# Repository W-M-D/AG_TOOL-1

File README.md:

# AG_TOOL-1

One of my first from scratch electronic projects was a electrical ac heater with a thermocouple based control system. After needing some for work I decided to see if I could find a premade solution. I was very disappointed with my search. They all cost thousands of dollars and lacked raspberry pis. Since then I have set out to create an open source all-in-one heating system with logging and automatic control ( timing controlled runs auto shutoff etc). This is what I have come up with so far.

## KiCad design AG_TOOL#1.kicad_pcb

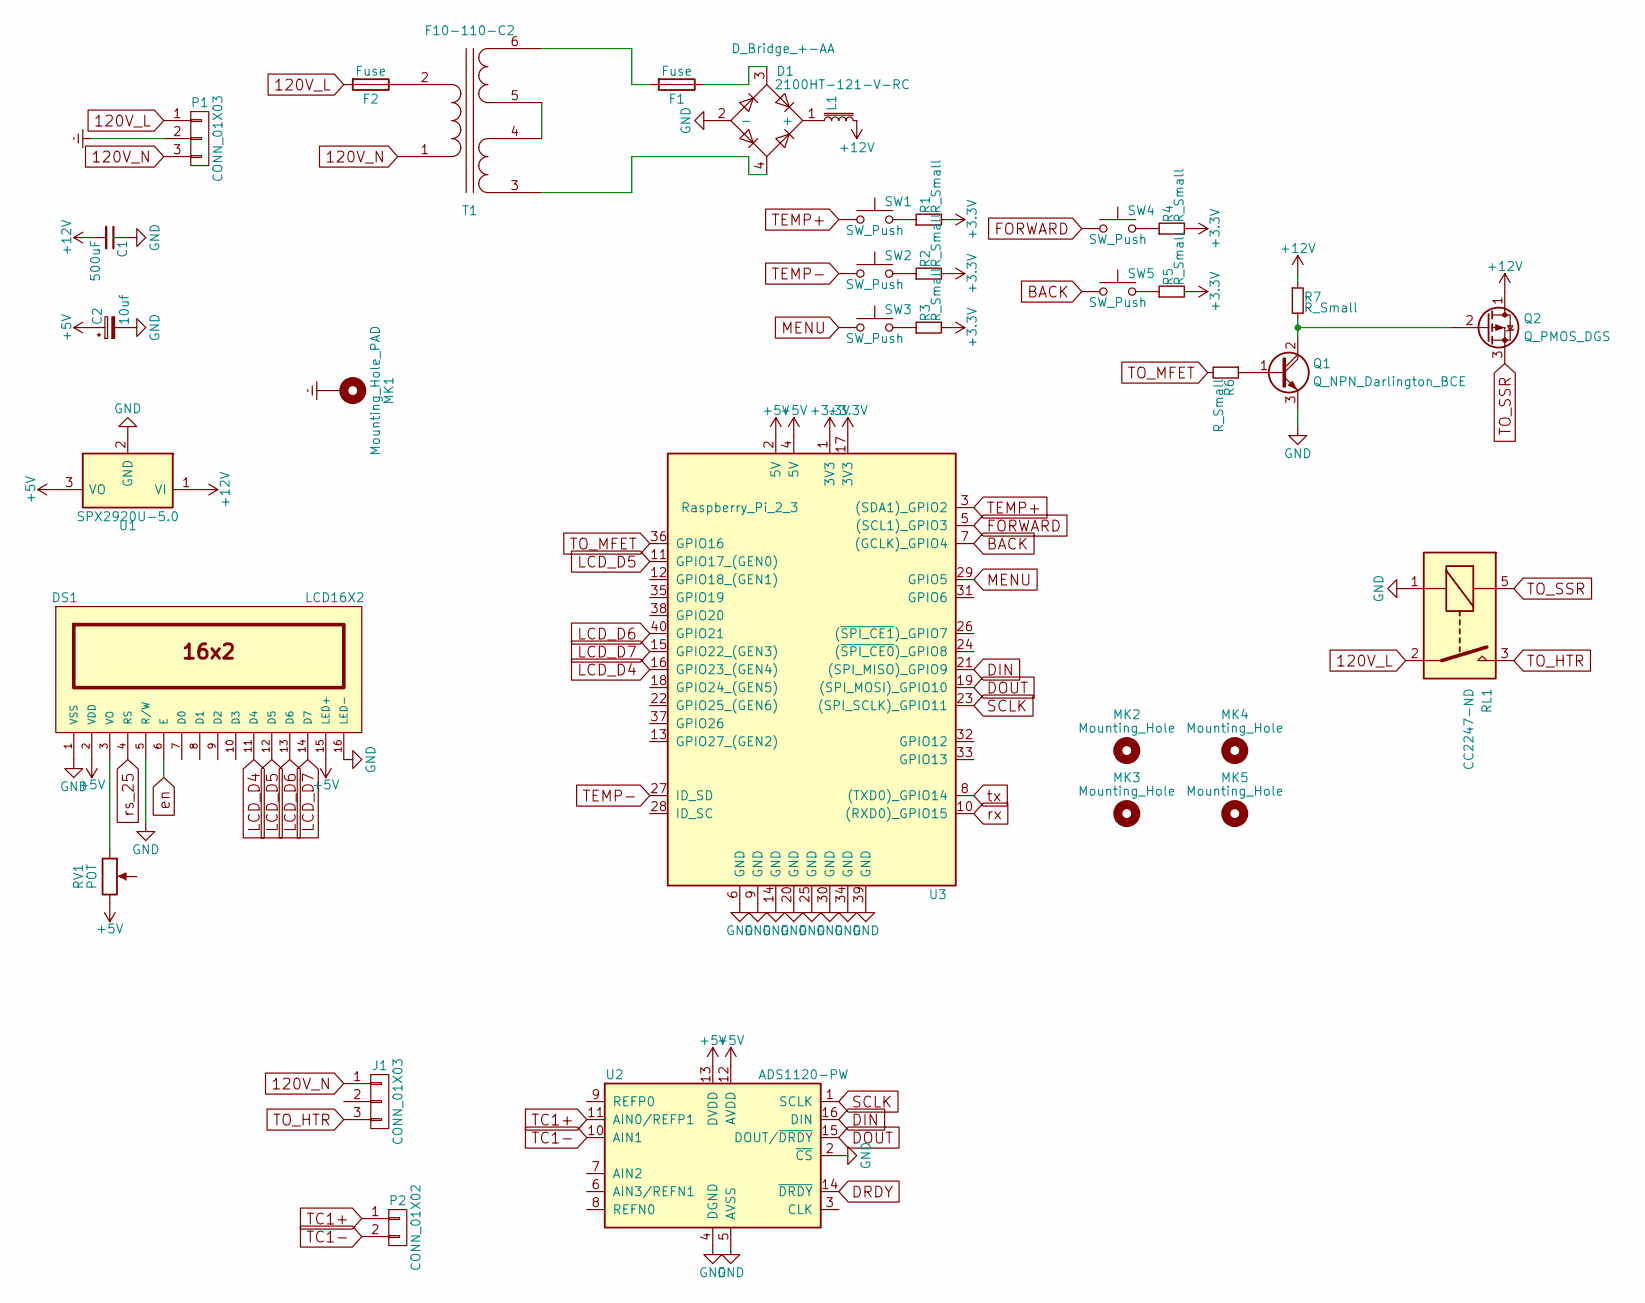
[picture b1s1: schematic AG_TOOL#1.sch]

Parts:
C1: 500uF; CP_Radial_D10.0mm_P3.50mm
C2: 10uf; C_1206
D1: D_Bridge_+-AA; Diode_Bridge_15.7x15.7
DS1: LCD16X2; Pin_Header_Straight_2x08_Pitch2.00mm
F1: Fuse; Fuse_0679H
F2: Fuse; Fuseholder_ATO_Blade_littlefuse_Pudenz_2_Pin
J1: CONN_01X03; SDF-30J
L1: 2100HT-121-V-RC; Choke_Toroid_horizontal_Diameter3-5mm_Amidon-T12
MK1: Mounting_Hole_PAD; MountingHole_4mm
MK2, MK3, MK4, MK5: Mounting_Hole; MountingHole_4mm
P1: CONN_01X03; 703W-0053
P2: CONN_01X02; K_ANSI_THERMOCOUPLE_SOCKET_PCB
Q1: Q_NPN_Darlington_BCE; SOT-23
Q2: Q_PMOS_DGS; SOT-23
R1, R2, R3, R4, R5, R6, R7: R_Small; R_0402
RL1: CC2247-ND; MCX240A5R
RV1: POT; Potentiometer_Bourns_3005_Angular_ScrewFront
SW1, SW2, SW3, SW4, SW5: SW_Push; SW_SPST_B3S-1000
T1: F10-110-C2
U1: SPX2920U-5.0; SOT-223-3Lead_TabPin2
U2: ADS1120-PW; TSSOP-16_4.4x5mm_Pitch0.65mm
U3: Raspberry_Pi_2_3; Pin_Header_Angled_2x20_Pitch2.00mm

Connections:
120V_L: F2.2, P1.1, RL1.2
120V_N: J1.1, P1.3, T1.1 (AA)
+3V3: R1.2, R2.2, R3.2, R4.2, R5.2, U3.1 (3V3), U3.17 (3V3)
+5V: C2.1, DS1.2 (VDD), DS1.15 (LED+), RV1.3, U1.3 (VO), U2.12 (AVDD), U2.13 (DVDD), U3.2 (5V), U3.4 (5V)
+12V: C1.2, L1.2, Q2.1 (D), R7.1, U1.1 (VI)
BACK: SW5.1, U3.7 ((GCLK)_GPIO4)
DIN: U2.16 (DIN), U3.21 ((SPI_MISO)_GPIO9)
DOUT: U2.15 (DOUT/~DRDY), U3.19 ((SPI_MOSI)_GPIO10)
DRDY: U2.14 (~DRDY)
Earth: MK1.1, P1.2
FORWARD: SW4.1, U3.5 ((SCL1)_GPIO3)
GND: C1.1, C2.2, D1.2 (-), DS1.1 (VSS), DS1.5 (R/W), DS1.16 (LED-), Q1.3 (E), RL1.1, U1.2 (GND), U2.2 (~CS), U2.4 (DGND), U2.5 (AVSS), U3.6 (GND), U3.9 (GND), U3.14 (GND), U3.20 (GND), U3.25 (GND), U3.30 (GND), U3.34 (GND), U3.39 (GND)
LCD_D4: DS1.11 (D4), U3.16 (GPIO23_(GEN4))
LCD_D5: DS1.12 (D5), U3.11 (GPIO17_(GEN0))
LCD_D6: DS1.13 (D6), U3.40 (GPIO21)
LCD_D7: DS1.14 (D7), U3.15 (GPIO22_(GEN3))
MENU: SW3.1, U3.29 (GPIO5)
unnamed: D1.1 (+), L1.1
unnamed: D1.3, F1.1
unnamed: D1.4, T1.3 (SA)
unnamed: DS1.3 (VO), RV1.1
unnamed: F1.2, T1.6 (SD)
unnamed: F2.1, T1.2 (AB)
unnamed: Q1.1 (B), R6.1
unnamed: Q1.2 (C), Q2.2 (G), R7.2
unnamed: R1.1, SW1.2
unnamed: R2.1, SW2.2
unnamed: R3.1, SW3.2
unnamed: R4.1, SW4.2
unnamed: R5.1, SW5.2
unnamed: T1.4 (SB), T1.5 (SC)
SCLK: U2.1 (SCLK), U3.23 ((SPI_SCLK)_GPIO11)
TC1+: P2.1, U2.11 (AIN0/REFP1)
TC1-: P2.2, U2.10 (AIN1)
TEMP+: SW1.1, U3.3 ((SDA1)_GPIO2)
TEMP-: SW2.1, U3.27 (ID_SD)
TO_HTR: J1.3, RL1.3
TO_MFET: R6.2, U3.36 (GPIO16)
TO_SSR: Q2.3 (S), RL1.5
en: DS1.6 (E)
rs_25: DS1.4 (RS)
rx: U3.10 ((RXD0)_GPIO15)
tx: U3.8 ((TXD0)_GPIO14)

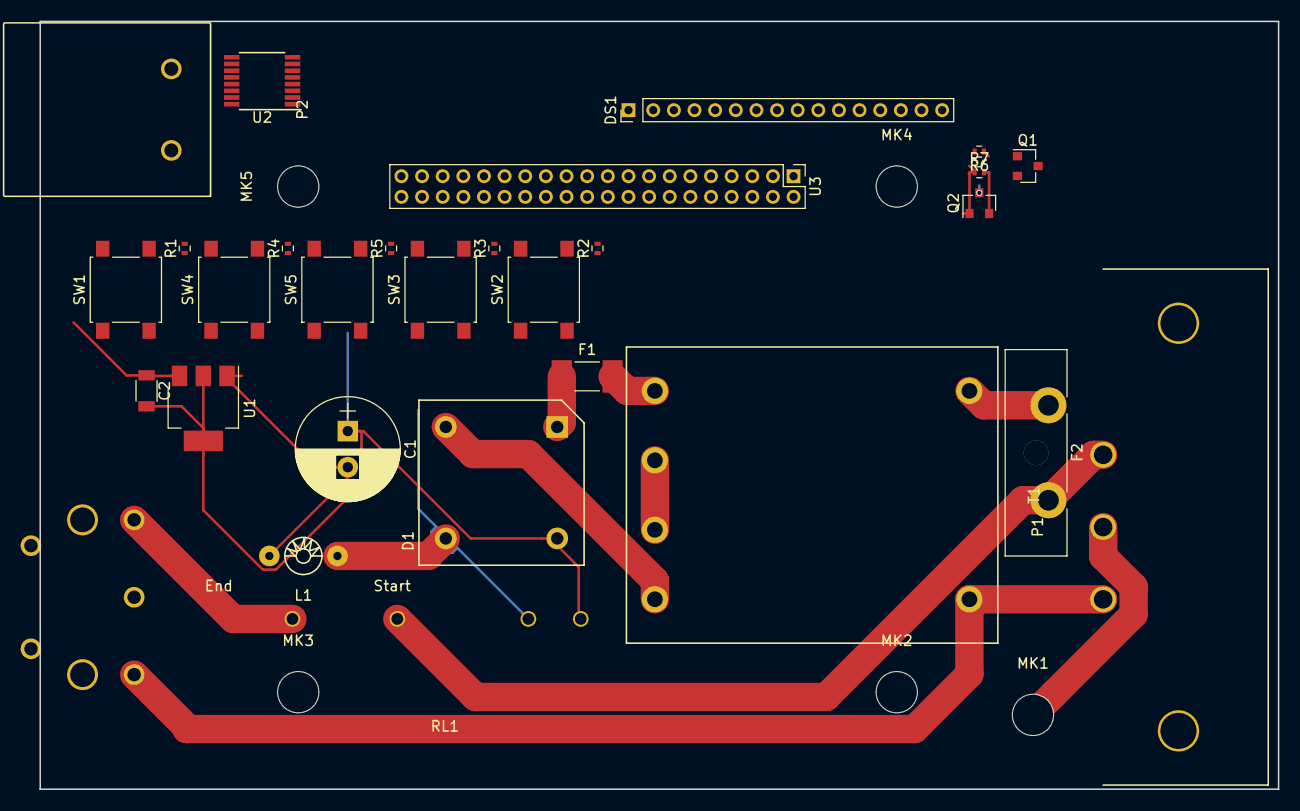
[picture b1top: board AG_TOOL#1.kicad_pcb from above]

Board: 2 copper layers, 120.0 x 74.4 mm, 34 parts (0 on the bottom side), 37 nets.

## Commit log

2017-08-19 init commit
2017-08-19 updating readme
2017-08-19 Adding in another fuse for the 120v line and a choke for the dc output
2017-08-22 well i need to go to sleep now but i added in a din connector for the heater output and started routing a little it's comming together nicely
2017-08-27 changed some parts
